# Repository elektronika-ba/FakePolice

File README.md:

# FakePolice
Remotely activated blinking lights (Atmel, Nordic)

https://hackaday.io/project/186051-street-racing-silencer

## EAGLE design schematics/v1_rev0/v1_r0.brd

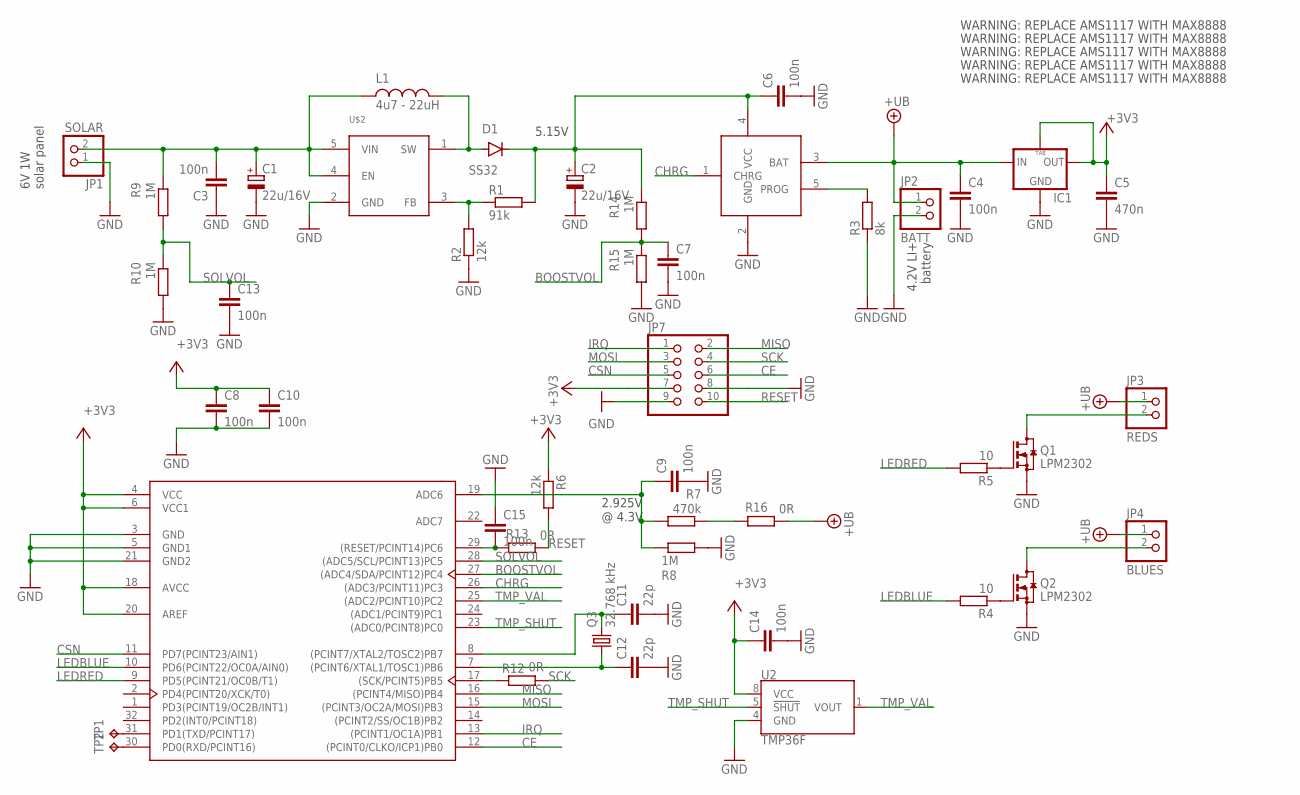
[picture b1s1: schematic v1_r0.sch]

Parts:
C1, C2: 22u/16V; CT6032
C3, C4, C6, C7, C8, C9, C10, C13, C14, C15: 100n; C0603
C5: 470n; C0603
C11, C12: 22p; C0603
D1: SS32; SMB
IC1: LM1117; SOT223
JP1: SOLAR; 1X02
JP2: BATT; 1X02
JP3: REDS; 1X02
JP4: BLUES; 1X02
JP7: PINHD-2X5; 2X05
L1: 4u7 - 22uH; DS1608
Q1, Q2: LPM2302; SOT23
Q3: 32.768 kHz; CTS406
R1: 91k; R0603
R2, R6: 12k; R0603
R3: 8k; R0603
R4, R5: 10; R0603
R7: 470k; R0603
R8, R9, R10, R14, R15: 1M; R0603
R12, R13, R16: 0R; 0204/5
TP1, TP2: TPB1,27; B1,27
U1: ATMEGA*; TQFP-32
U2: TMP36F; SOIC-8
U$1: LTC4054
U$2: SB6284; SOT23-6

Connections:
+3V3: C5.1, C8.1, C10.1, C14.1, IC1.2 (OUT), IC1.4 (TAB), JP7.7, R6.1, U1.4 (VCC), U1.6 (VCC1), U1.18 (AVCC), U1.20 (AREF), U2.8 (VCC)
+UB: C4.1, IC1.3 (IN), JP2.1, JP3.1, JP4.1, R16.1, U$1.3 (BAT)
BOOSTVOL: C7.1, R14.2, R15.1, U1.27 ((ADC4/SDA/PCINT12)PC4)
BOOSTVOL1: C2.+, C6.1, D1.C, R1.2, R14.1, U$1.4 (VCC)
CE: JP7.6, U1.12 ((PCINT0/CLKO/ICP1)PB0)
CHRG: U1.26 ((ADC3/PCINT11)PC3), U$1.1 (CHRG)
CSN: JP7.5, U1.11 (PD7(PCINT23/AIN1))
GND: C1.-, C2.-, C3.1, C4.2, C5.2, C6.2, C7.2, C8.2, C9.2, C10.2, C11.2, C12.2, C13.2, C14.2, C15.1, IC1.1 (GND), JP1.1, JP2.2, JP7.8, JP7.9, Q1.2 (S), Q2.2 (S), R2.1, R3.1, R8.2, R10.2, R15.2, U1.3 (GND), U1.5 (GND1), U1.21 (GND2), U2.4 (GND), U$1.2 (GND), U$2.2 (GND)
IRQ: JP7.1, U1.13 ((PCINT1/OC1A)PB1)
LEDBLUE: R4.2, U1.10 (PD6(PCINT22/OC0A/AIN0))
LEDRED: R5.2, U1.9 (PD5(PCINT21/OC0B/T1))
MISO: JP7.2, U1.16 ((PCINT4/MISO)PB4)
MOSI: JP7.3, U1.15 ((PCINT3/OC2A/MOSI)PB3)
unnamed: R3.2, U$1.5 (PROG)
unnamed: D1.A, L1.P$1, U$2.1 (SW)
unnamed: R1.1, R2.2, U$2.3 (FB)
unnamed: Q2.1 (G), R4.1
unnamed: Q1.1 (G), R5.1
unnamed: JP3.2, Q1.3 (D)
unnamed: JP4.2, Q2.3 (D)
unnamed: R12.1, U1.17 ((SCK/PCINT5)PB5)
unnamed: C9.1, R7.2, R8.1, U1.19 (ADC6)
unnamed: R7.1, R16.2
unnamed: TP1.TP, U1.31 (PD1(TXD/PCINT17))
unnamed: C12.1, Q3.1, U1.7 ((PCINT6/XTAL1/TOSC1)PB6)
unnamed: C11.1, Q3.3 (2), U1.8 ((PCINT7/XTAL2/TOSC2)PB7)
unnamed: TP2.TP, U1.30 (PD0(RXD/PCINT16))
unnamed: C15.2, R13.2, U1.29 ((RESET/PCINT14)PC6)
RESET: JP7.10, R6.2, R13.1
SCK: JP7.4, R12.2
SOLIN: C1.+, C3.2, JP1.2, L1.P$2, R9.1, U$2.4 (EN), U$2.5 (VIN)
SOLVOL: C13.1, R9.2, R10.1, U1.28 ((ADC5/SCL/PCINT13)PC5)
TMP_SHUT: U1.23 ((ADC0/PCINT8)PC0), U2.5 (!SHUT)
TMP_VAL: U1.25 ((ADC2/PCINT10)PC2), U2.1 (VOUT)

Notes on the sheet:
6V 1W solar panel
5.15V
4.2V LI+ battery
2.925V @ 4.3V
WARNING: REPLACE AMS1117 WITH MAX8888

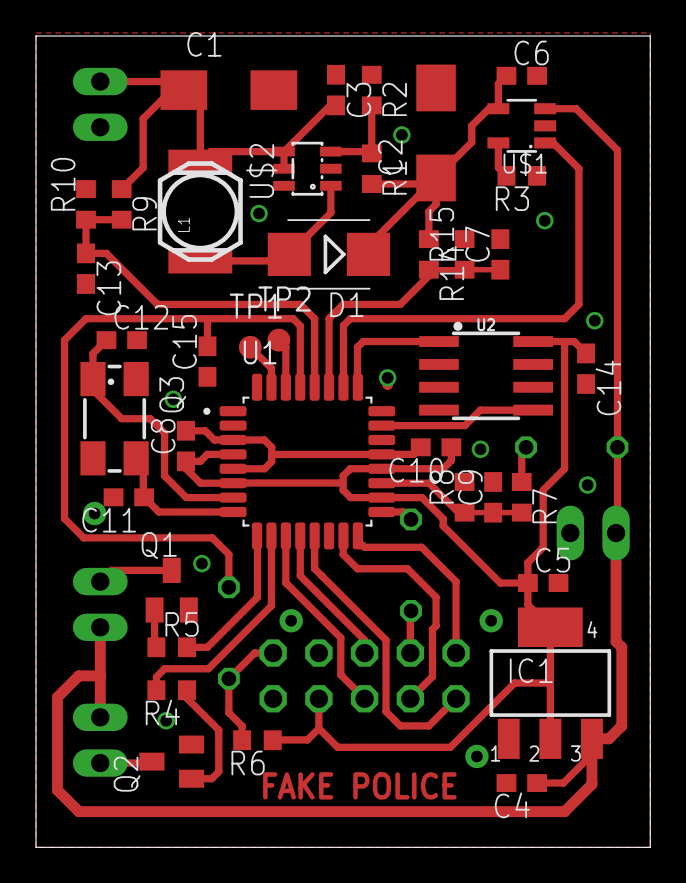
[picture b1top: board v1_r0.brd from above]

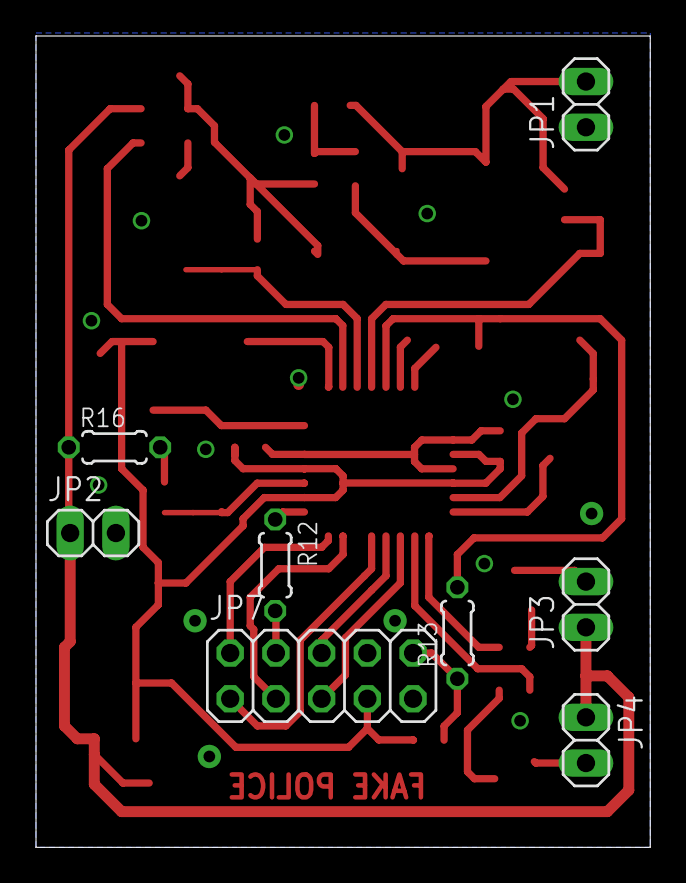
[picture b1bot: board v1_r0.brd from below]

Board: 2 copper layers, 34.1 x 45.1 mm, 47 parts (8 on the bottom side), 34 nets.

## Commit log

2022-06-13 progress
2022-06-14 njeh
2022-06-15 workaing
2022-06-16 blabla
2022-06-16 before testing
2022-06-16 added other files
2022-06-16 things starting to work
    still in major debug stage
2022-06-17 playing around
2022-06-17 Atmel Studio 7
    upgraded to atmel studio 7, fixed a bug with SYNC
2022-06-19 things happening
2022-06-19 popo
2022-06-20 alpha working
2022-06-20 added raspberrypi python test code
    added raspberrypi part of project for controlling the thing
2022-06-25 beta version finished
2022-06-28 param for config of police light blinker
2022-06-29 added more features to RF protocol
2022-06-29 bug fixes, new python test1.py
2022-06-29 new schematics
2022-06-29 even newser schematics
    WARNING: replace AMS1117 with MAX8888

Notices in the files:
parts and their libraries:
SparkFun-Sensors: Licensing: Creative Commons ShareAlike 4.0 International - https://creativecommons.org/licenses/by-sa/4.0
